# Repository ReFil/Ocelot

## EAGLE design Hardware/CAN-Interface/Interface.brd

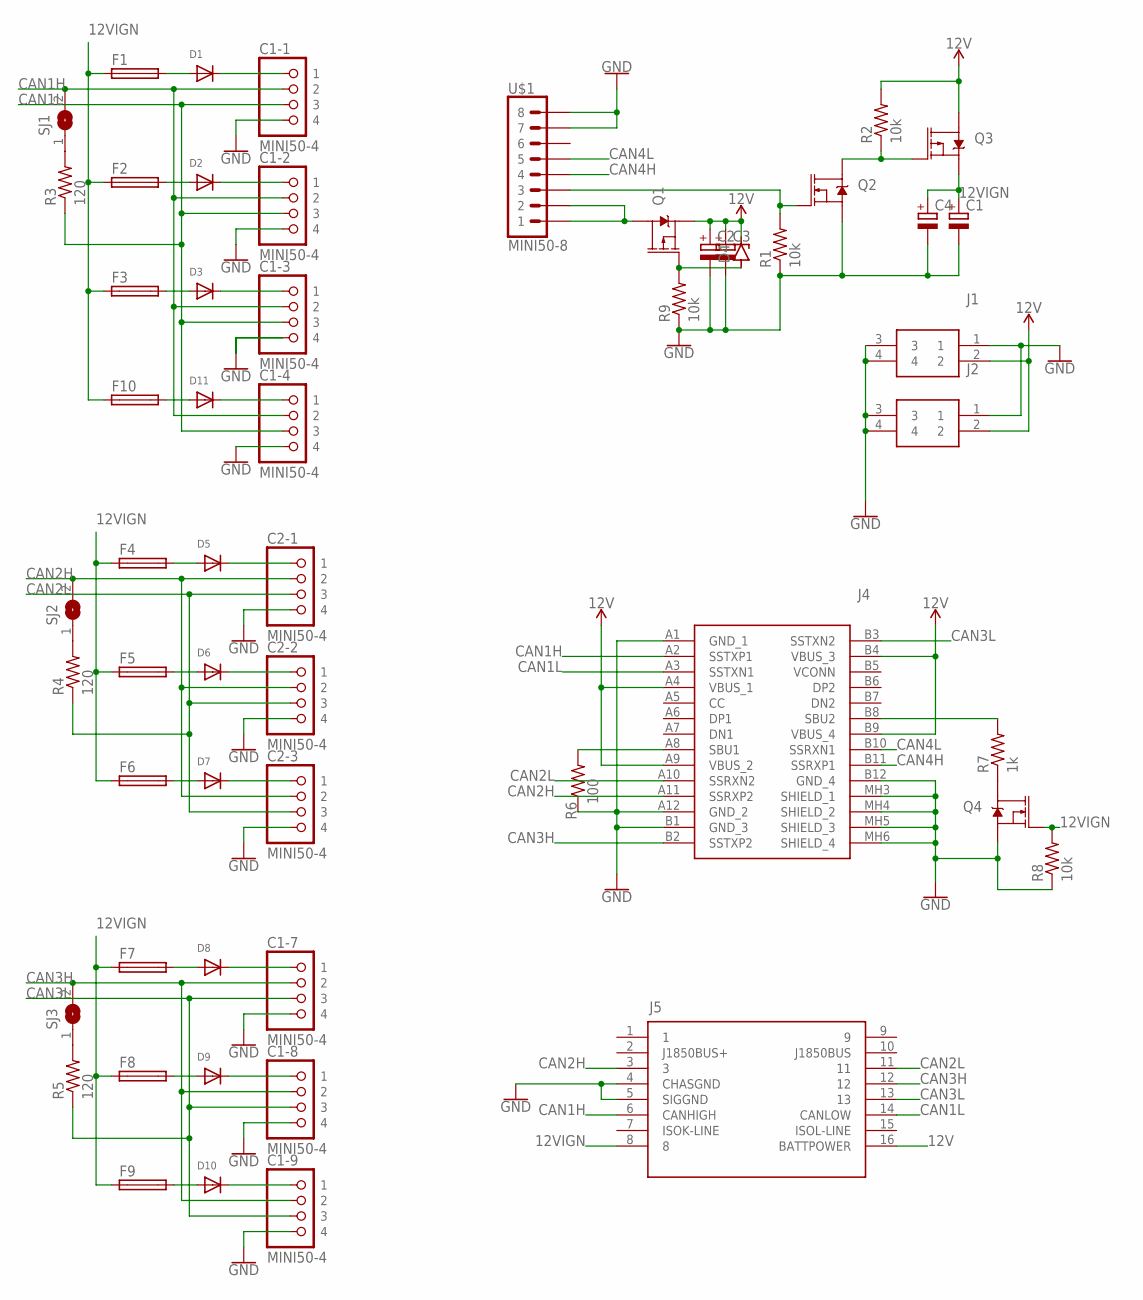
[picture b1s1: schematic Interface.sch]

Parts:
C1, C2: CPOL-EU153CLV-1010; 153CLV-1010
C1-1, C1-2, C1-3, C1-4, C1-7, C1-8, C1-9, C2-1, C2-2, C2-3: MINI50-4; MINI50
C3, C4: CPOL-EU153CLV-0505; 153CLV-0505
D1, D2, D3, D5, D6, D7, D8, D9, D10, D11: DIODESOD-323F; SOD-323F
D4: ZENER_DO-219-AB(SOD123F); SODFL3718X115
F1, F2, F3, F4, F5, F6, F7, F8, F9, F10: FUSE_CHIP-1206(3216-METRIC); FUSC3215X82N
J1, J2: 34912-8020; 0349128020
J4: 632722110112
J5: OBDII-FEMALEFEMALE; OBDII-FEMALE
Q1, Q3: 6.5A/20V/35mΩ; SO08
Q2, Q4: 5.8A/30V/35mΩ; SOT23-3
R1, R2, R8, R9: 10k; 0402-R
R3, R4, R5: 120; 0402-R
R6: 100; 0402-R
R7: 1k; 0402-R
SJ1, SJ2, SJ3: SJ
U$1: MINI50-8

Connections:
12V: C2.+, C3.+, D4.2 (C), J1.2, J2.2, J4.A4 (VBUS_1), J4.A9 (VBUS_2), J4.B4 (VBUS_3), J4.B9 (VBUS_4), J5.16 (BATTPOWER), Q1.1 (S), Q1.2 (S), Q1.3 (S), Q3.5 (D), Q3.6 (D), Q3.7 (D), Q3.8 (D), R2.2
12VIGN: C1.+, C4.+, F1.1, F2.1, F3.1, F4.1, F5.1, F6.1, F7.1, F8.1, F9.1, F10.1, J5.8, Q3.1 (S), Q3.2 (S), Q3.3 (S), Q4.1 (G), R8.2
CAN1H: C1-1.3 (2), C1-2.3 (2), C1-3.3 (2), C1-4.3 (2), J4.A2 (SSTXP1), J5.6 (CANHIGH), SJ1.2
CAN1L: C1-1.2 (3), C1-2.2 (3), C1-3.2 (3), C1-4.2 (3), J4.A3 (SSTXN1), J5.14 (CANLOW), R3.1
CAN2H: C2-1.3 (2), C2-2.3 (2), C2-3.3 (2), J4.A11 (SSRXP2), J5.3, SJ2.2
CAN2L: C2-1.2 (3), C2-2.2 (3), C2-3.2 (3), J4.A10 (SSRXN2), J5.11, R4.1
CAN3H: C1-7.3 (2), C1-8.3 (2), C1-9.3 (2), J4.B2 (SSTXP2), J5.12, SJ3.2
CAN3L: C1-7.2 (3), C1-8.2 (3), C1-9.2 (3), J4.B3 (SSTXN2), J5.13, R5.1
CAN4H: J4.B11 (SSRXP1), U$1.P$4 (4)
CAN4L: J4.B10 (SSRXN1), U$1.P$5 (5)
GND: C1.-, C1-1.1 (4), C1-2.1 (4), C1-3.1 (4), C1-4.1 (4), C1-7.1 (4), C1-8.1 (4), C1-9.1 (4), C2.-, C2-1.1 (4), C2-2.1 (4), C2-3.1 (4), C3.-, C4.-, J1.1, J1.3, J1.4, J2.1, J2.3, J2.4, J4.A1 (GND_1), J4.A12 (GND_2), J4.B1 (GND_3), J4.B12 (GND_4), J4.MH3 (SHIELD_1), J4.MH4 (SHIELD_2), J4.MH5 (SHIELD_3), J4.MH6 (SHIELD_4), J5.4 (CHASGND), J5.5 (SIGGND), Q2.2 (S), Q4.2 (S), R1.1, R6.1, R8.1, R9.1, U$1.P$7 (7), U$1.P$8 (8)
unnamed: D1.A, F1.2
unnamed: C1-1.4 (1), D1.C
unnamed: D2.A, F2.2
unnamed: C1-2.4 (1), D2.C
unnamed: D3.A, F3.2
unnamed: C1-3.4 (1), D3.C
unnamed: R3.2, SJ1.1
unnamed: D5.A, F4.2
unnamed: C2-1.4 (1), D5.C
unnamed: Q1.5 (D), Q1.6 (D), Q1.7 (D), Q1.8 (D), U$1.P$1 (1), U$1.P$2 (2)
unnamed: D6.A, F5.2
unnamed: Q2.1 (G), R1.2, U$1.P$3 (3)
unnamed: C2-2.4 (1), D6.C
unnamed: D7.A, F6.2
unnamed: Q2.3 (D), Q3.4 (G), R2.1
unnamed: C2-3.4 (1), D7.C
unnamed: R4.2, SJ2.1
unnamed: D8.A, F7.2
unnamed: C1-7.4 (1), D8.C
unnamed: D9.A, F8.2
unnamed: C1-8.4 (1), D9.C
unnamed: D10.A, F9.2
unnamed: C1-9.4 (1), D10.C
unnamed: R5.2, SJ3.1
unnamed: J4.B8 (SBU2), R7.2
unnamed: D4.1 (A), Q1.4 (G), R9.2
unnamed: D11.A, F10.2
unnamed: C1-4.4 (1), D11.C
unnamed: Q4.3 (D), R7.1
unnamed: J4.A8 (SBU1), R6.2

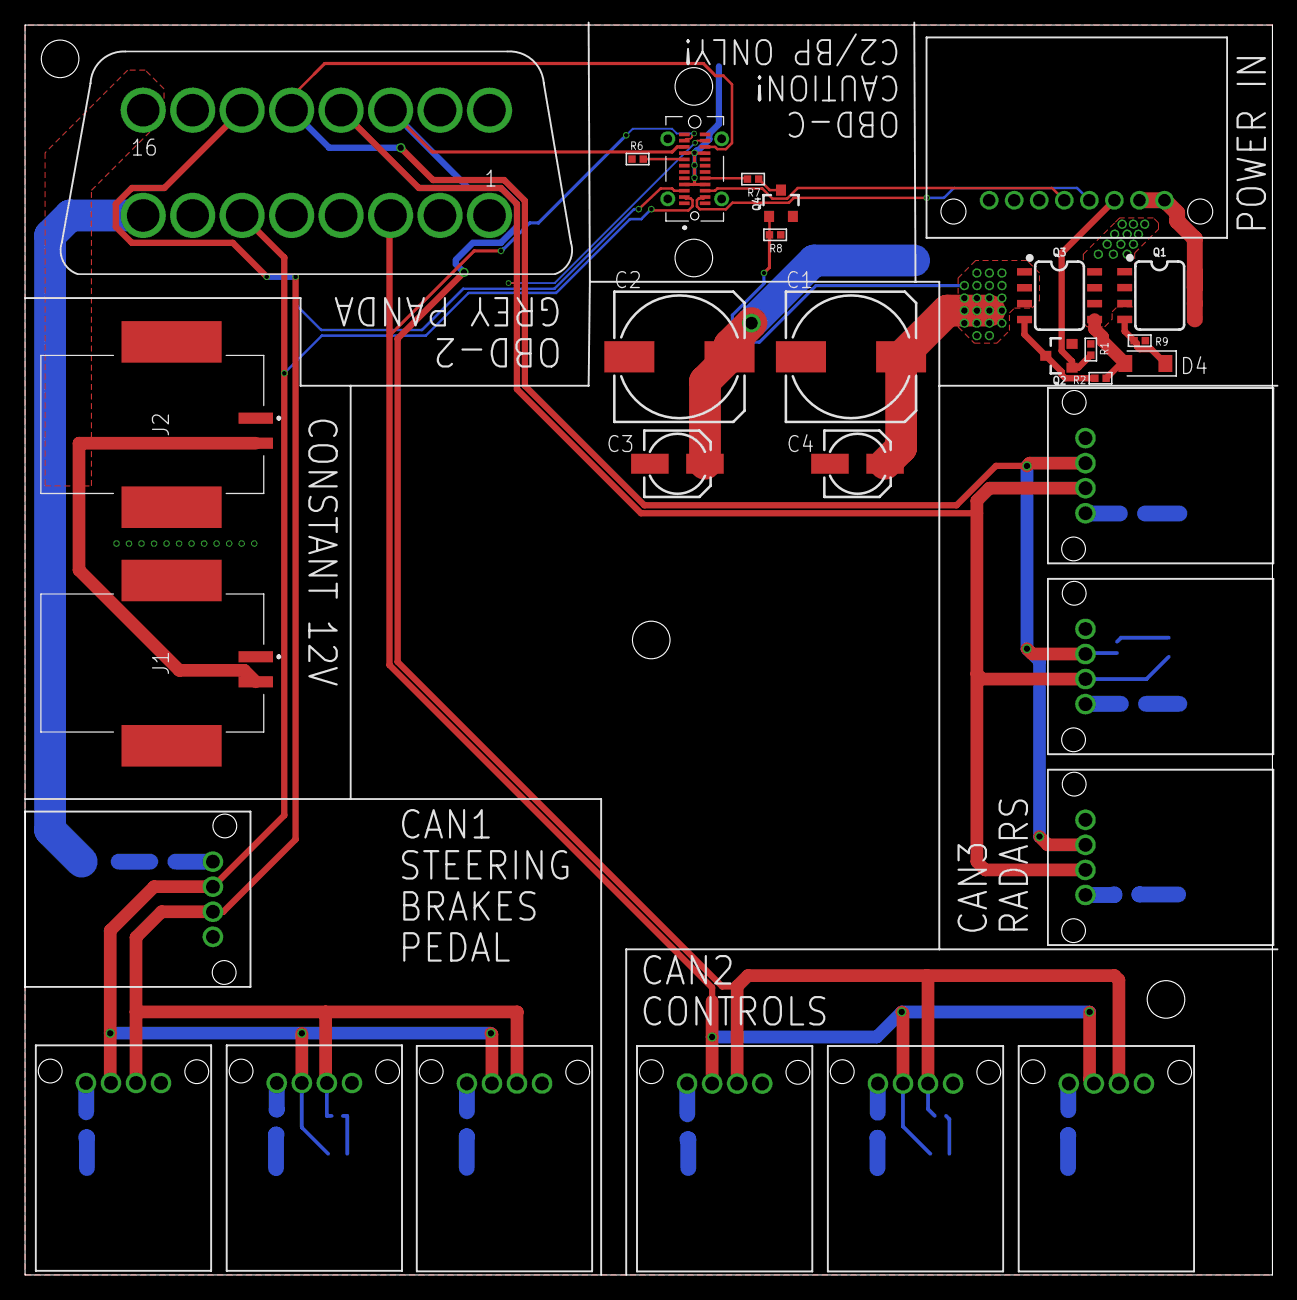
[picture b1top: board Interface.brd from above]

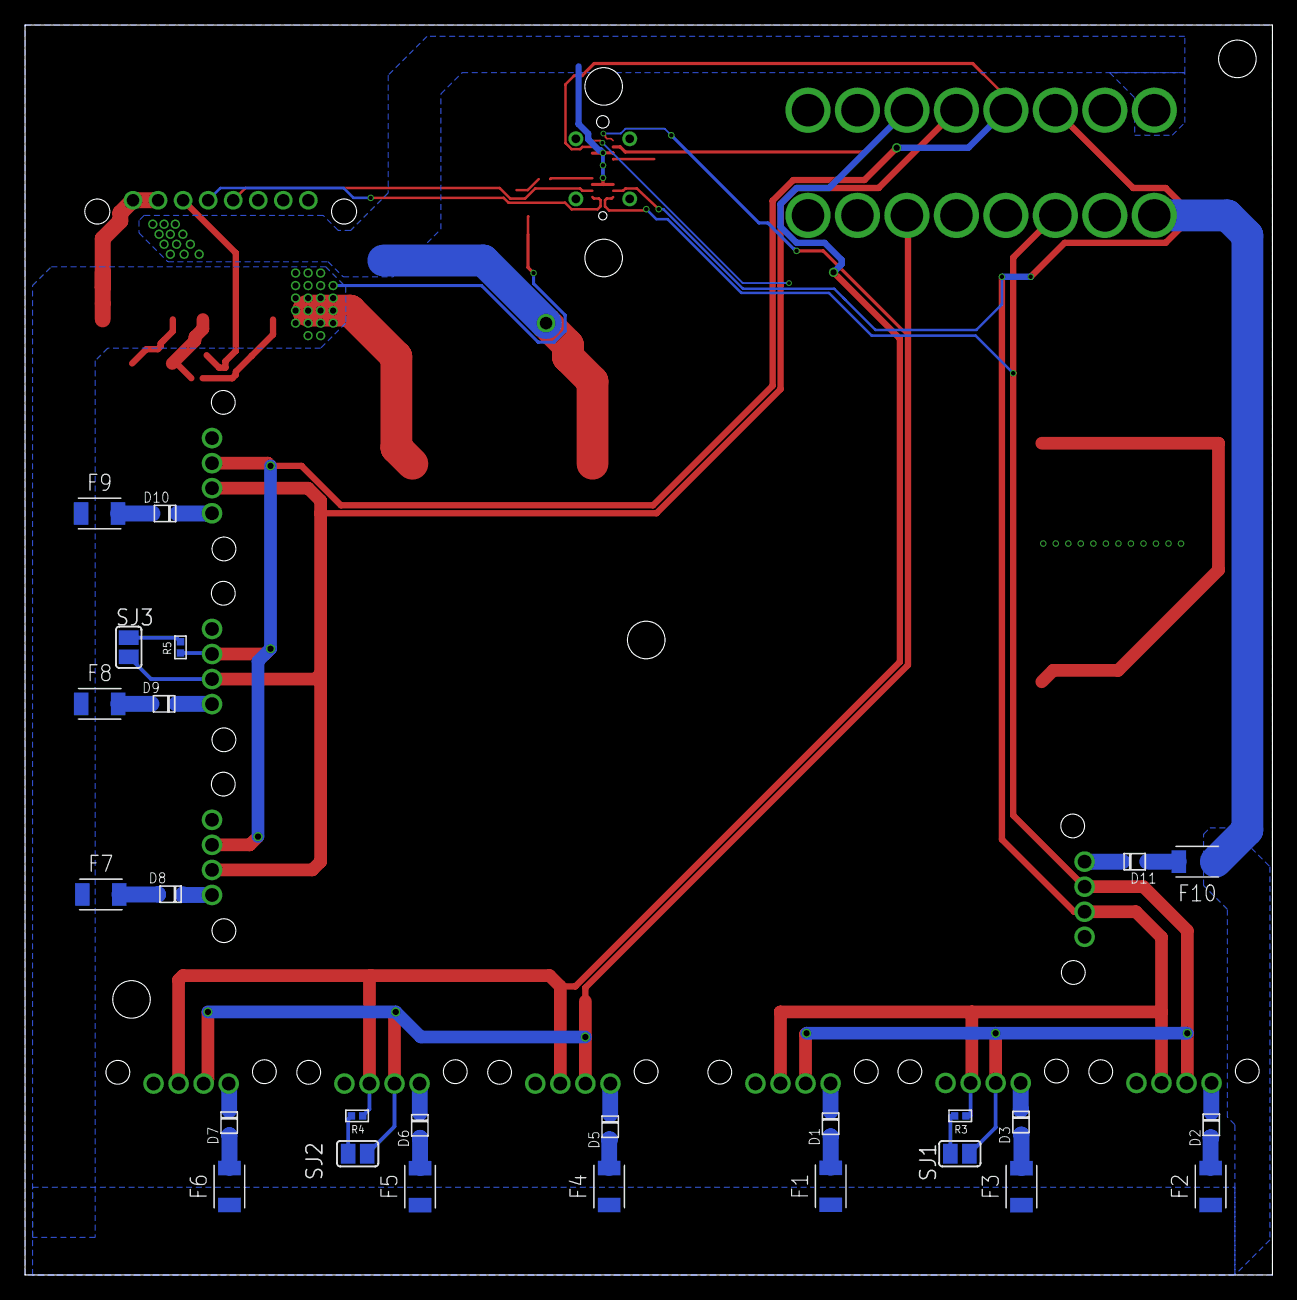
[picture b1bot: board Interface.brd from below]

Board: 2 copper layers, 99.6 x 99.8 mm, 56 parts (26 on the bottom side), 41 nets.

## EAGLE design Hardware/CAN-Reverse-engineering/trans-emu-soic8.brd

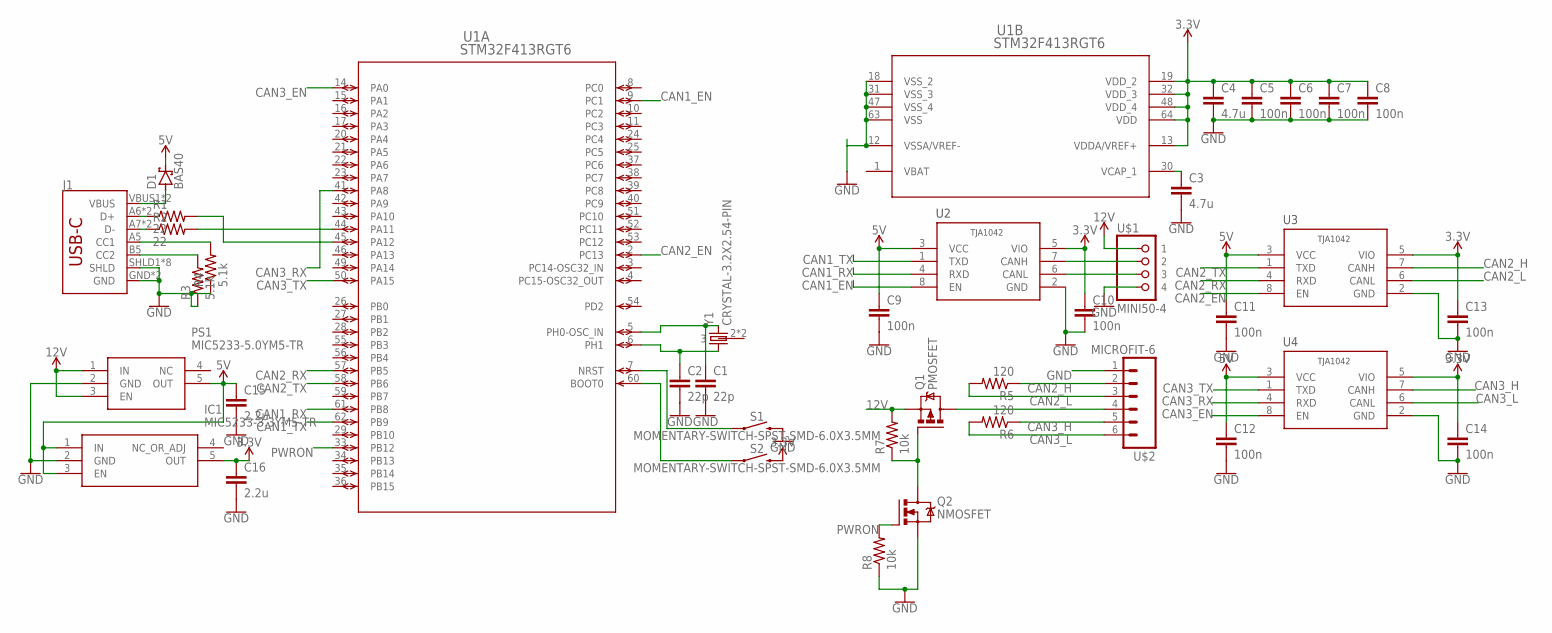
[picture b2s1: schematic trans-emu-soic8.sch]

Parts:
C1, C2: 22p; 0603-C
C3, C4: 4.7u; 0603-C
C5, C6, C7, C8, C9, C10, C11, C12, C13, C14: 100n; 0603-C
C15, C16: 2.2u; 0603-C
D1: BAS40; SOT23
IC1: MIC5233-3.3YM5-TR; SOT95P280X145-5N
J1: USB-C-BREAKOUT_SPARKFUN-CONNECTORS_USB_C16PIN; USB-C-BREAKOUT_SPARKFUN-CONNECTORS_USB-C-16P
PS1: MIC5233-5.0YM5-TR; SOT95P280X145-5N
Q1: PMOSFET; SOT23
Q2: NMOSFET; SOT23
R1, R2: 22; 0402-R
R3, R4: 5.1k; 0402-R
R5, R6: 120; 0402-R
R7, R8: 10k; 0402-R
S1, S2: MOMENTARY-SWITCH-SPST-SMD-6.0X3.5MM; TACTILE_SWITCH_SMD_6.0X3.5MM
U1: STM32F413RGT6; LQFP64-10X10MM
U2, U3, U4: TJA1042; NXP_SEMICONDUCTORS_TJA1042T-3-CM_118_0
U$1: MINI50-4; MINI50
U$2: MICROFIT-6
Y1: CRYSTAL-3.2X2.54-PIN; XTAL-3.2X2.5

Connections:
3.3V: C4.1, C5.1, C6.1, C7.1, C8.1, C10.1, C13.1, C14.1, C16.1, IC1.5 (OUT), S2.2, U1.13 (VDDA/VREF+), U1.19 (VDD_2), U1.32 (VDD_3), U1.48 (VDD_4), U1.64 (VDD), U2.5 (VIO), U3.5 (VIO), U4.5 (VIO)
5V: C9.1, C11.1, C12.1, C15.1, D1.3 (C), IC1.1 (IN), IC1.3 (EN), PS1.5 (OUT), U2.3 (VCC), U3.3 (VCC), U4.3 (VCC)
12V: PS1.1 (IN), PS1.3 (EN), Q1.2 (S), R7.2, U$1.4 (1)
CAN1_EN: U1.9 (PC1), U2.8 (EN)
CAN1_RX: U1.61 (PB8), U2.4 (RXD)
CAN1_TX: U1.62 (PB9), U2.1 (TXD)
CAN2_EN: U1.2 (PC13), U3.8 (EN)
CAN2_H: R5.1, U3.7 (CANH), U$2.2
CAN2_L: R5.2, U3.6 (CANL), U$2.3
CAN2_RX: U1.57 (PB5), U3.4 (RXD)
CAN2_TX: U1.58 (PB6), U3.1 (TXD)
CAN3_EN: U1.14 (PA0), U4.8 (EN)
CAN3_H: R6.1, U4.7 (CANH), U$2.5
CAN3_L: R6.2, U4.6 (CANL), U$2.6
CAN3_RX: U1.41 (PA8), U4.4 (RXD)
CAN3_TX: U1.50 (PA15), U4.1 (TXD)
GND: C1.2, C2.2, C3.2, C4.2, C5.2, C6.2, C7.2, C8.2, C9.2, C10.2, C11.2, C12.2, C13.2, C14.2, C15.2, C16.2, IC1.2 (GND), J1.GND, J1.GND2 (GND), J1.SHLD1 (SHLD), J1.SHLD2 (SHLD), J1.SHLD3 (SHLD), J1.SHLD4 (SHLD), J1.SHLD5 (SHLD), J1.SHLD6 (SHLD), J1.SHLD7 (SHLD), J1.SHLD8 (SHLD), PS1.2 (GND), Q2.2 (S), R3.1, R4.1, R8.1, S1.2, U1.12 (VSSA/VREF-), U1.18 (VSS_2), U1.31 (VSS_3), U1.47 (VSS_4), U1.63 (VSS), U2.2 (GND), U3.2 (GND), U4.2 (GND), U$1.1 (4), U$2.1
unnamed: C1.1, U1.5 (PH0-OSC_IN), Y1.3 (2)
unnamed: C2.1, U1.6 (PH1), Y1.1
unnamed: R2.2, U1.44 (PA11)
unnamed: R1.2, U1.45 (PA12)
unnamed: D1.1 (A), J1.VBUS1 (VBUS), J1.VBUS2 (VBUS)
unnamed: J1.A5 (CC1), R4.2
unnamed: J1.B5 (CC2), R3.2
unnamed: S1.1, U1.7 (NRST)
unnamed: S2.1, U1.60 (BOOT0)
unnamed: J1.A6 (D+), J1.B6 (D+), R1.1
unnamed: J1.A7 (D-), J1.B7 (D-), R2.1
unnamed: U2.7 (CANH), U$1.3 (2)
unnamed: C3.1, U1.30 (VCAP_1)
unnamed: U2.6 (CANL), U$1.2 (3)
unnamed: Q1.3 (D), U$2.4
unnamed: Q1.1 (G), Q2.3 (D), R7.1
PWRON: Q2.1 (G), R8.2, U1.33 (PB12)
VBAT: U1.1 (VBAT)

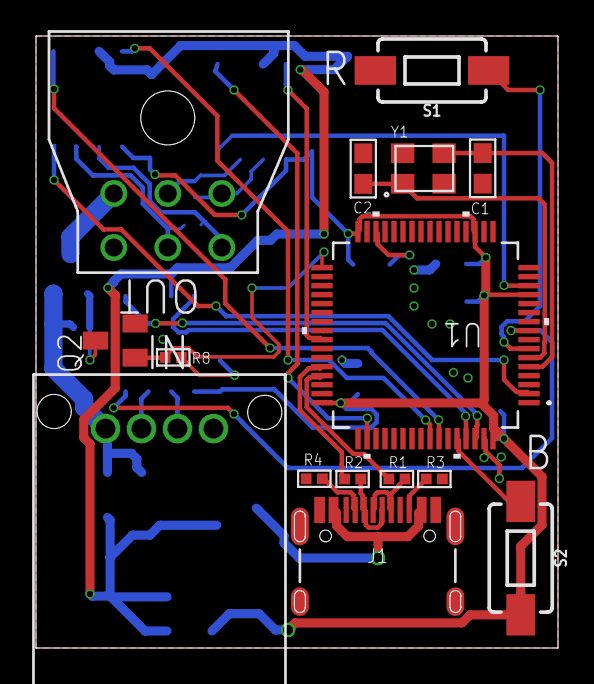
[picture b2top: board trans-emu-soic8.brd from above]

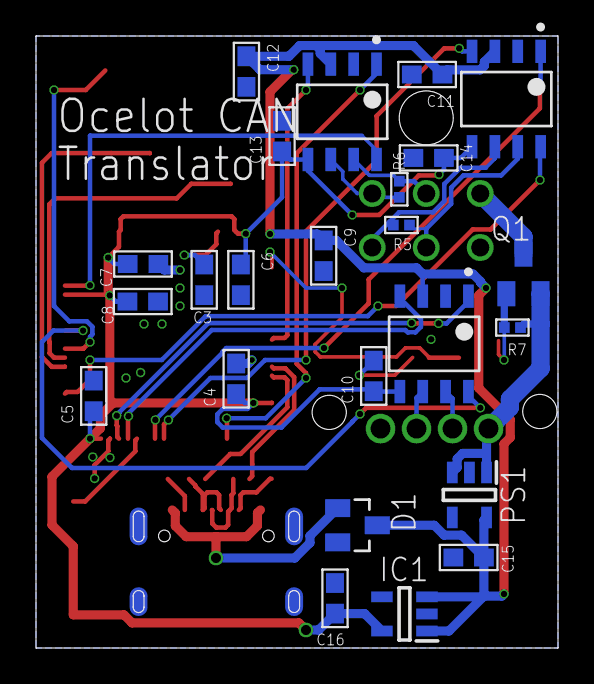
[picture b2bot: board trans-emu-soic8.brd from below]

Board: 2 copper layers, 29.0 x 34.0 mm, 39 parts (24 on the bottom side), 34 nets.

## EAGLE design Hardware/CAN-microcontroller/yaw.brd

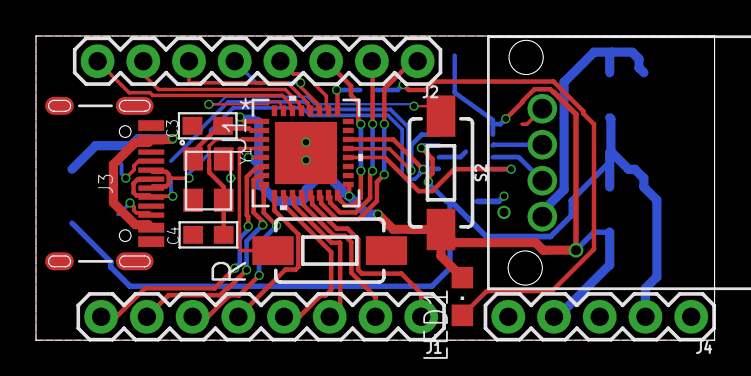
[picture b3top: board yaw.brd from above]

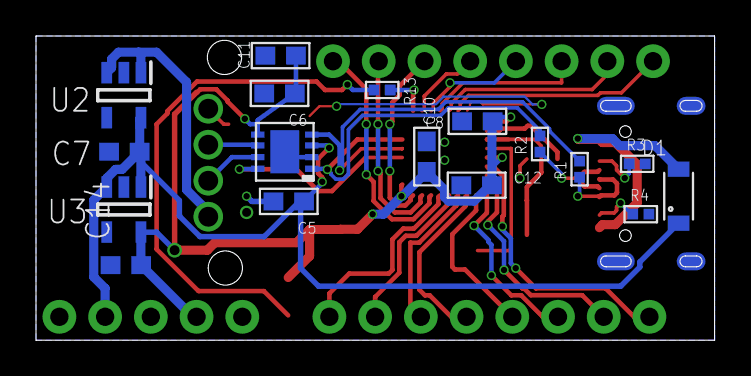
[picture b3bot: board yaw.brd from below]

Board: 2 copper layers, 37.7 x 16.9 mm, 29 parts (17 on the bottom side), 36 nets.

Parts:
C3, C4: 22p; 0603-C
C5, C6, C8, C10, C11: 100nF; 0603-C
C7, C14: 2.2u; C0603
C12: 4.7uF; 0603-C
D1: DIODEDB2W40100L; SOD-123F
J1, J2: 1X08
J3: USB-C-BREAKOUT_SPARKFUN-CONNECTORS_USB-C-16P
J4: 1X05
LED1: CHIPLED_0805
R1, R2, R3, R4: 0402-R
R13: 220; 0402-R
S1, S2: MOMENTARY-SWITCH-SPST-SMD-6.0X3.5MM; TACTILE_SWITCH_SMD_6.0X3.5MM
U1: STM32F042K6U6; UFQFPN32-5X5MM
U2: MIC5233-5.0YM5-TR; SOT95P280X145-5N
U3: MIC5233-3.3YM5-TR; SOT95P280X145-5N
U4: TJA1042HVSON; HVSON8
U$2: MINI50-4; MINI50
Y1: 16MHz; XTAL-3.2X2.5

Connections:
3V3: C6.1, C8.1, C10.1, C11.1, C12.1, C14.1, J4.4, LED1.A, S2.2, U1.1, U1.5, U1.17, U3.5, U4.5
5V: C5.1, C7.1, D1.1, J4.2, U2.5, U3.1, U3.3, U4.3
12V: U2.1, U2.3, U$2.4
CAN1_EN: U1.20, U4.8
CAN1_H: U4.7, U$2.3
CAN1_L: U4.6, U$2.2
CAN1_RX: R1.2, U1.21, U4.4
CAN1_TX: R2.2, U1.22, U4.1
GND: C3.2, C4.2, C5.2, C6.2, C7.2, C8.2, C10.2, C11.2, C12.2, C14.2, J3.GND, J3.GND2, J3.SHLD1, J3.SHLD2, J3.SHLD3, J3.SHLD4, J3.SHLD5, J3.SHLD6, J3.SHLD7, J3.SHLD8, J4.1, J4.3, J4.5, R3.2, R4.2, S1.2, U1.33, U2.2, U3.2, U4.2, U4.PAD, U$2.1, Y1.2, Y1.4
LEDG: R13.1, U1.25
unnamed: J1.1, U1.13
unnamed: C3.1, U1.2, Y1.1
unnamed: J1.2, U1.12
unnamed: J1.3, U1.11
unnamed: J1.4, U1.10
unnamed: S2.1, U1.31
unnamed: J1.5, U1.9
unnamed: J1.6, U1.8
unnamed: J1.7, U1.7
unnamed: J1.8, U1.6
unnamed: J2.1, U1.14
unnamed: J2.2, U1.15
unnamed: J2.3, U1.16
unnamed: J2.4, U1.26
unnamed: J2.5, U1.27
unnamed: J2.6, U1.28
unnamed: J2.7, U1.29
unnamed: J2.8, U1.30
unnamed: D1.2, J3.VBUS1, J3.VBUS2
unnamed: J3.A6, J3.B6, R1.1
unnamed: J3.A7, J3.B7, R2.1
unnamed: J3.A5, R3.1
unnamed: J3.B5, R4.1
unnamed: LED1.C, R13.2
unnamed: C4.1, U1.3, Y1.3
NRST: S1.1, U1.4

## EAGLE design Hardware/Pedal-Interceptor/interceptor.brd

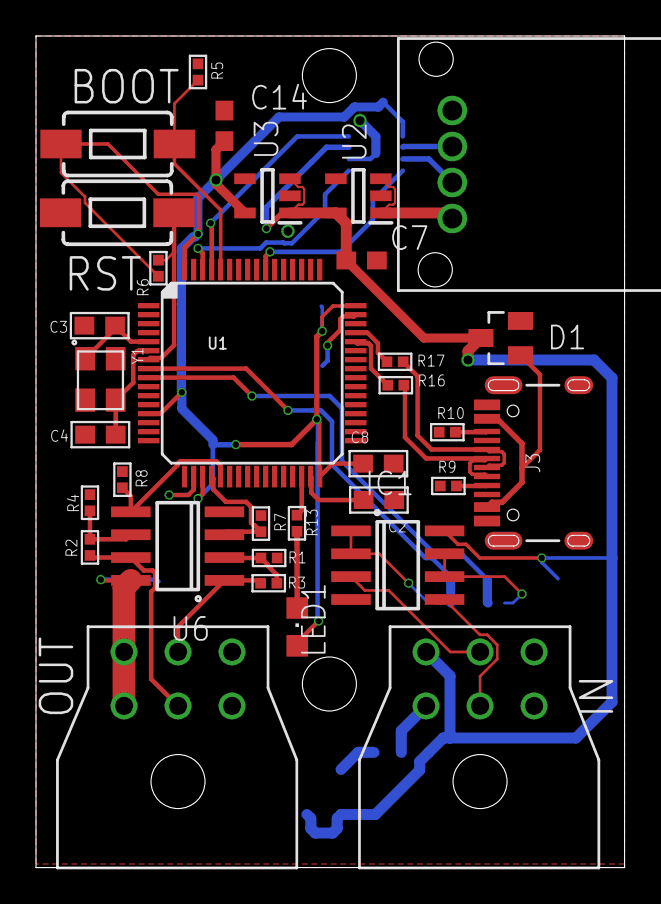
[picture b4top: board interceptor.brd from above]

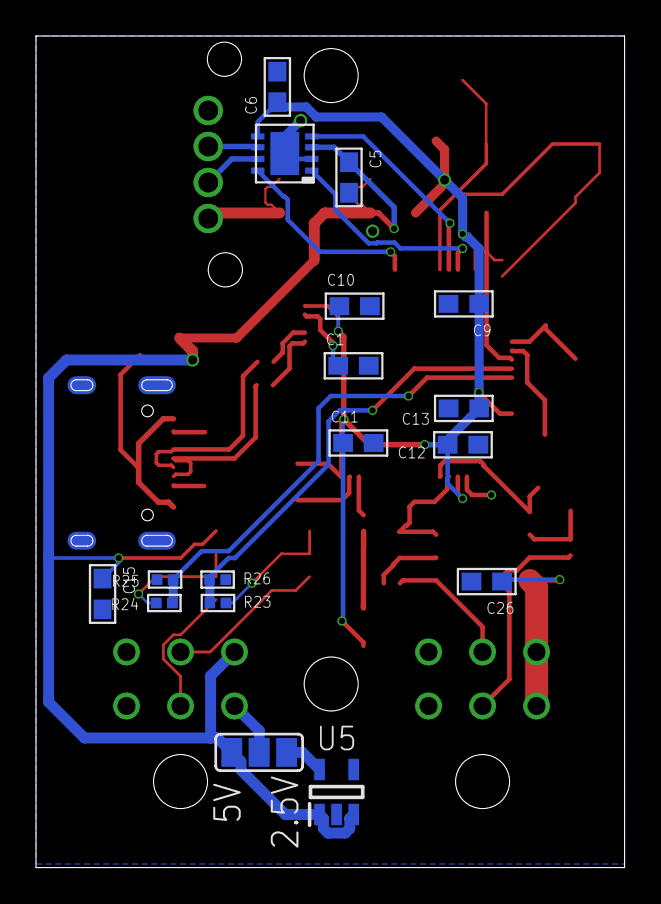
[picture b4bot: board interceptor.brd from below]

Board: 2 copper layers, 32.7 x 46.2 mm, 50 parts (17 on the bottom side), 39 nets.

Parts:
C1, C2: 2.2uF; 0603-C
C3, C4: 12pF; 0603-C
C5, C6, C8, C9, C10, C11, C13, C15, C26: 100nF; 0603-C
C7, C14: 2.2u; C0603
C12: 4.7uF; 0603-C
D1: BAS40; SOT23
IC1: LM358D; SO08
J3: USB-C-BREAKOUT_SPARKFUN-CONNECTORS_USB-C-16P
LED1: CHIPLED_0805
R1, R2, R3, R4, R5, R6, R7, R8: 10k; 0402-R
R9, R10: 5.1k; 0402-R
R13: 220; 0402-R
R16, R17: 22; 0402-R
R23, R24, R25, R26: 1k; 0402-R
S1, S2: MOMENTARY-SWITCH-SPST-SMD-6.0X3.5MM; TACTILE_SWITCH_SMD_6.0X3.5MM
SJ1: SJ_2
U1: STM32-M-64-LQFP; LQFP64
U2, U5: MIC5233-5.0YM5-TR; SOT95P280X145-5N
U3: MIC5233-3.3YM5-TR; SOT95P280X145-5N
U4: TJA1042HVSON; HVSON8
U6: MCP6002; SO08
U$1, U$3: MICROFIT-6
U$2: MINI50-4; MINI50
Y1: 16MHz; XTAL-3.2X2.5

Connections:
3V3: C6.1, C8.1, C9.1, C10.1, C11.1, C12.1, C13.1, C14.1, LED1.A, R6.1, S2.1, U1.13, U1.19, U1.32, U1.48, U1.64, U3.5, U4.5
5V: C5.1, C7.1, C15.1, D1.3, IC1.8, SJ1.3, U2.5, U3.1, U3.3, U4.3, U5.1, U5.3, U$3.3
12V: U2.1, U2.3, U$2.4
ACCEL1: IC1.3, U$3.2
ACCEL2: IC1.5, U$3.5
CAN1_EN: U1.55, U4.8
CAN1_H: U4.7, U$2.3
CAN1_L: U4.6, U$2.2
CAN1_RX: U1.61, U4.4
CAN1_TX: U1.62, U4.1
DAC1: R3.2, U6.1, U$1.2
DAC2: R2.2, U6.7, U$1.5
DACV: C26.1, U6.8, U$1.3, U$1.6
GND: C1.2, C2.1, C3.2, C4.2, C5.2, C6.2, C7.2, C8.2, C9.2, C10.2, C11.2, C12.2, C13.2, C14.2, C15.2, C26.2, IC1.4, J3.GND, J3.GND2, J3.SHLD1, J3.SHLD2, J3.SHLD3, J3.SHLD4, J3.SHLD5, J3.SHLD6, J3.SHLD7, J3.SHLD8, R1.1, R4.1, R5.1, R7.1, R8.1, R9.1, R10.1, R25.2, R26.2, S1.1, U1.12, U1.18, U1.28, U1.63, U2.2, U3.2, U4.2, U4.PAD, U5.2, U6.4, U$1.1, U$1.4, U$2.1, U$3.1, U$3.4, Y1.2, Y1.4
LEDG: R13.1, U1.30
unnamed: C3.1, U1.5, Y1.1
unnamed: R16.1, U1.44
unnamed: C4.1, U1.6, Y1.3
unnamed: R17.1, U1.45
unnamed: J3.A7, J3.B7, R16.2
unnamed: J3.A6, J3.B6, R17.2
unnamed: R5.2, S2.2, U1.60
unnamed: J3.A5, R9.2
unnamed: J3.B5, R10.2
unnamed: R6.2, S1.2, U1.7
unnamed: D1.1, J3.VBUS1, J3.VBUS2
unnamed: SJ1.2, U$3.6
unnamed: IC1.1, IC1.2, R23.2
unnamed: SJ1.1, U5.5
unnamed: IC1.6, IC1.7, R24.2
unnamed: R7.2, U1.20, U6.3
unnamed: R8.2, U1.21, U6.5
unnamed: R1.2, R3.1, U6.2
unnamed: R2.1, R4.2, U6.6
unnamed: LED1.C, R13.2
unnamed: R23.1, R26.1, U1.8
unnamed: R24.1, R25.1, U1.9
VCAP1: C2.2, U1.31
VCAP2: C1.1, U1.47

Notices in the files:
parts and their libraries:
SparkFun-DiscreteSemi: Licensing: Creative Commons ShareAlike 4.0 International - https://creativecommons.org/licenses/by-sa/4.0
COPYRIGHT: Copyright (C) 2018 Accelerated Designs. All rights reserved
